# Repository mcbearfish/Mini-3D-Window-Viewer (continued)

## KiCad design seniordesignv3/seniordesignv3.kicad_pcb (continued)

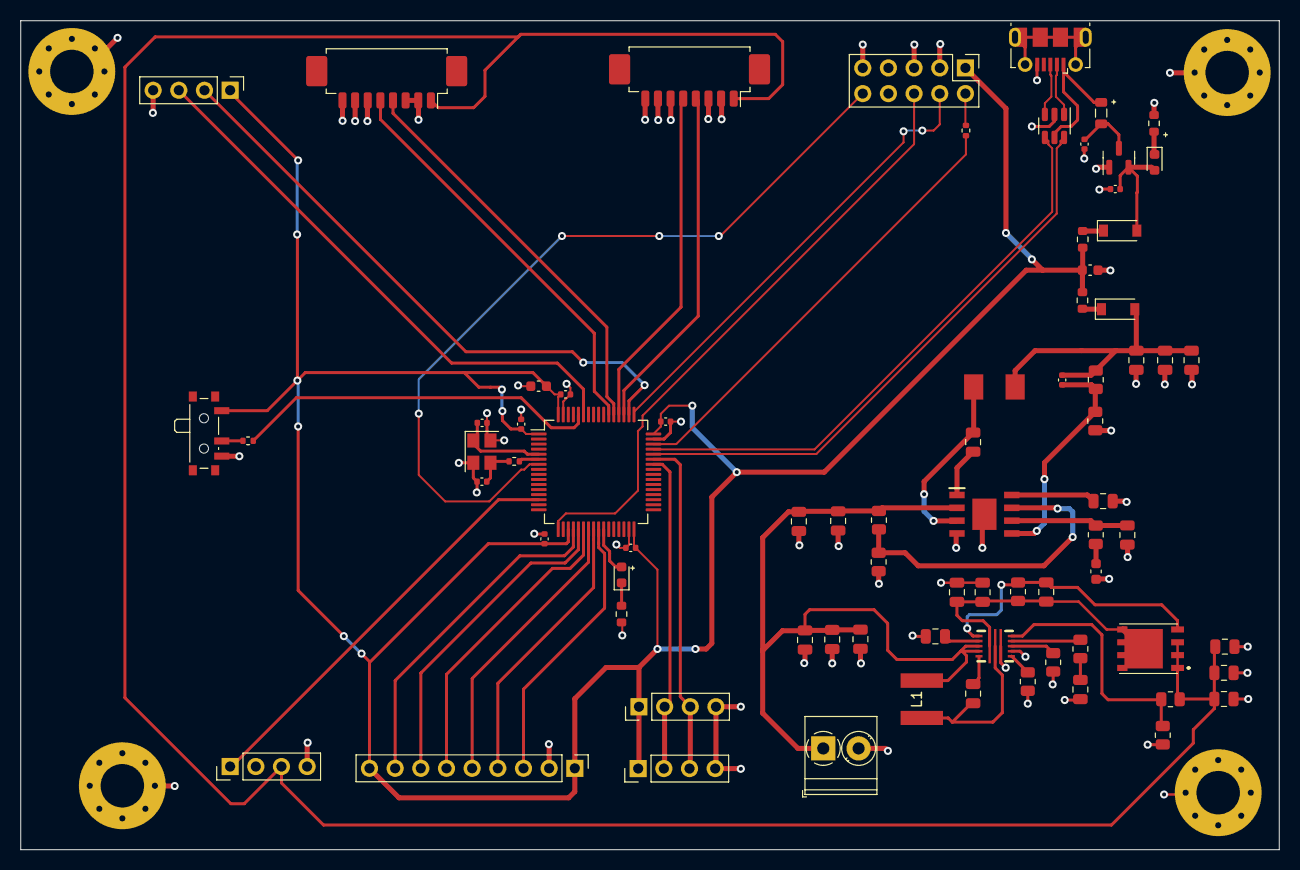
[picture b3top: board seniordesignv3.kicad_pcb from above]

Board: 2 copper layers, 124.6 x 82.0 mm, 80 parts (0 on the bottom side), 59 nets.

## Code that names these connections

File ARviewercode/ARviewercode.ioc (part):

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Mcu.Name=STM32F429VITx
Mcu.Package=LQFP100
Mcu.UserName=STM32F429VITx
PA0/WKUP.Signal=GPIO_Input
PA11.Mode=Device_Only
PA11.Signal=USB_OTG_FS_DM
PA12.Mode=Device_Only
PA12.Signal=USB_OTG_FS_DP
PA13.Mode=Trace_Asynchronous_SW
PA13.Signal=SYS_JTMS-SWDIO
PA14.Mode=Trace_Asynchronous_SW
PA14.Signal=SYS_JTCK-SWCLK
PA7.Signal=GPIO_Output
PB3.Mode=Trace_Asynchronous_SW
PB3.Signal=SYS_JTDO-SWO
PB6.Mode=I2C
PB6.Signal=I2C1_SCL
PB7.Mode=I2C
PB7.Signal=I2C1_SDA
PC0.Signal=GPIO_Output
PC1.Signal=GPIO_Output
PC2.Signal=GPIO_Output
PC3.Signal=GPIO_Output
PD0.Mode=16b-d1
PD0.Signal=FMC_D2
PD1.Mode=16b-d1
PD1.Signal=FMC_D3
PD10.Mode=16b-d1
PD10.Signal=FMC_D15
PD11.Mode=A16_1
PD11.Signal=FMC_A16
PD14.Mode=16b-d1
PD14.Signal=FMC_D0
PD15.Mode=16b-d1
PD15.Signal=FMC_D1
PD3.GPIOParameters=GPIO_Label
PD3.GPIO_Label=FMC_RST
PD3.Signal=GPIO_Output
PD4.Mode=Lcd1
PD4.Signal=FMC_NOE
PD5.Mode=Lcd1
PD5.Signal=FMC_NWE
PD7.Mode=NorPsramChipSelect1_1
PD7.Signal=FMC_NE1
PD8.Mode=16b-d1
PD8.Signal=FMC_D13
PD9.Mode=16b-d1
PD9.Signal=FMC_D14
PE0.GPIOParameters=GPIO_Label,GPIO_ModeDefaultEXTI
PE0.GPIO_Label=LIS3MDLTR_INT
PE0.GPIO_ModeDefaultEXTI=GPIO_MODE_IT_RISING_FALLING
PE0.Signal=GPXTI0
PE1.GPIOParameters=GPIO_Label,GPIO_ModeDefaultEXTI
PE1.GPIO_Label=LIS3MDLTR_DRDY
PE1.GPIO_ModeDefaultEXTI=GPIO_MODE_IT_RISING_FALLING
PE1.Signal=GPXTI1
PE10.Mode=16b-d1
PE10.Signal=FMC_D7
PE11.Mode=16b-d1
PE11.Signal=FMC_D8
PE12.Mode=16b-d1
PE12.Signal=FMC_D9
PE13.Mode=16b-d1
PE13.Signal=FMC_D10
PE14.Mode=16b-d1
PE14.Signal=FMC_D11
PE15.Mode=16b-d1
PE15.Signal=FMC_D12
PE2.GPIOParameters=GPIO_Label,GPIO_ModeDefaultEXTI
PE2.GPIO_Label=LSM6DR_INT1
PE2.GPIO_ModeDefaultEXTI=GPIO_MODE_IT_RISING_FALLING
PE2.Signal=GPXTI2
PE3.GPIOParameters=GPIO_Label,GPIO_ModeDefaultEXTI
PE3.GPIO_Label=LSM6DR_INT2
PE3.GPIO_ModeDefaultEXTI=GPIO_MODE_IT_RISING_FALLING
PE3.Signal=GPXTI3
PE7.Mode=16b-d1
PE7.Signal=FMC_D4
PE8.Mode=16b-d1
PE8.Signal=FMC_D5
PE9.Mode=16b-d1
PE9.Signal=FMC_D6
PH0/OSC_IN.Mode=HSE-External-Oscillator
PH0/OSC_IN.Signal=RCC_OSC_IN
PH1/OSC_OUT.Mode=HSE-External-Oscillator
PH1/OSC_OUT.Signal=RCC_OSC_OUT
RCC.HSE_VALUE=25000000
RCC.SYSCLKFreq_VALUE=16000000
board=custom

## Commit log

2026-04-07 Added code
